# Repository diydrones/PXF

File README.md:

PXF ( current boards are 1.4)
===

This is the new Repository for the PXF Linux AutoPilot. 

This Project will allow the porting of ArduPilot to Linux, allowing us to add a multitude of other features to the Autopilot.

The actual Autopilot code will still be in the ArduPilot repo.<a href="https://github.com/diydrones/ardupilot" title="https://github.com/diydrones/ardupilot" target="https://github.com/diydrones/ardupilot"> https://github.com/diydrones/ardupilot</a>

This Repo will house the Hardware Schematics, Datasheets, and software specific to the PXF project.

Version 1 of this project is a cape for the BBB.

This project is for developers, it will NOT be supported by the DIYDrones or Ardupilot support forums for general users. 

This means we do not expect that this board will be plug and play, nor do we intend it to be.

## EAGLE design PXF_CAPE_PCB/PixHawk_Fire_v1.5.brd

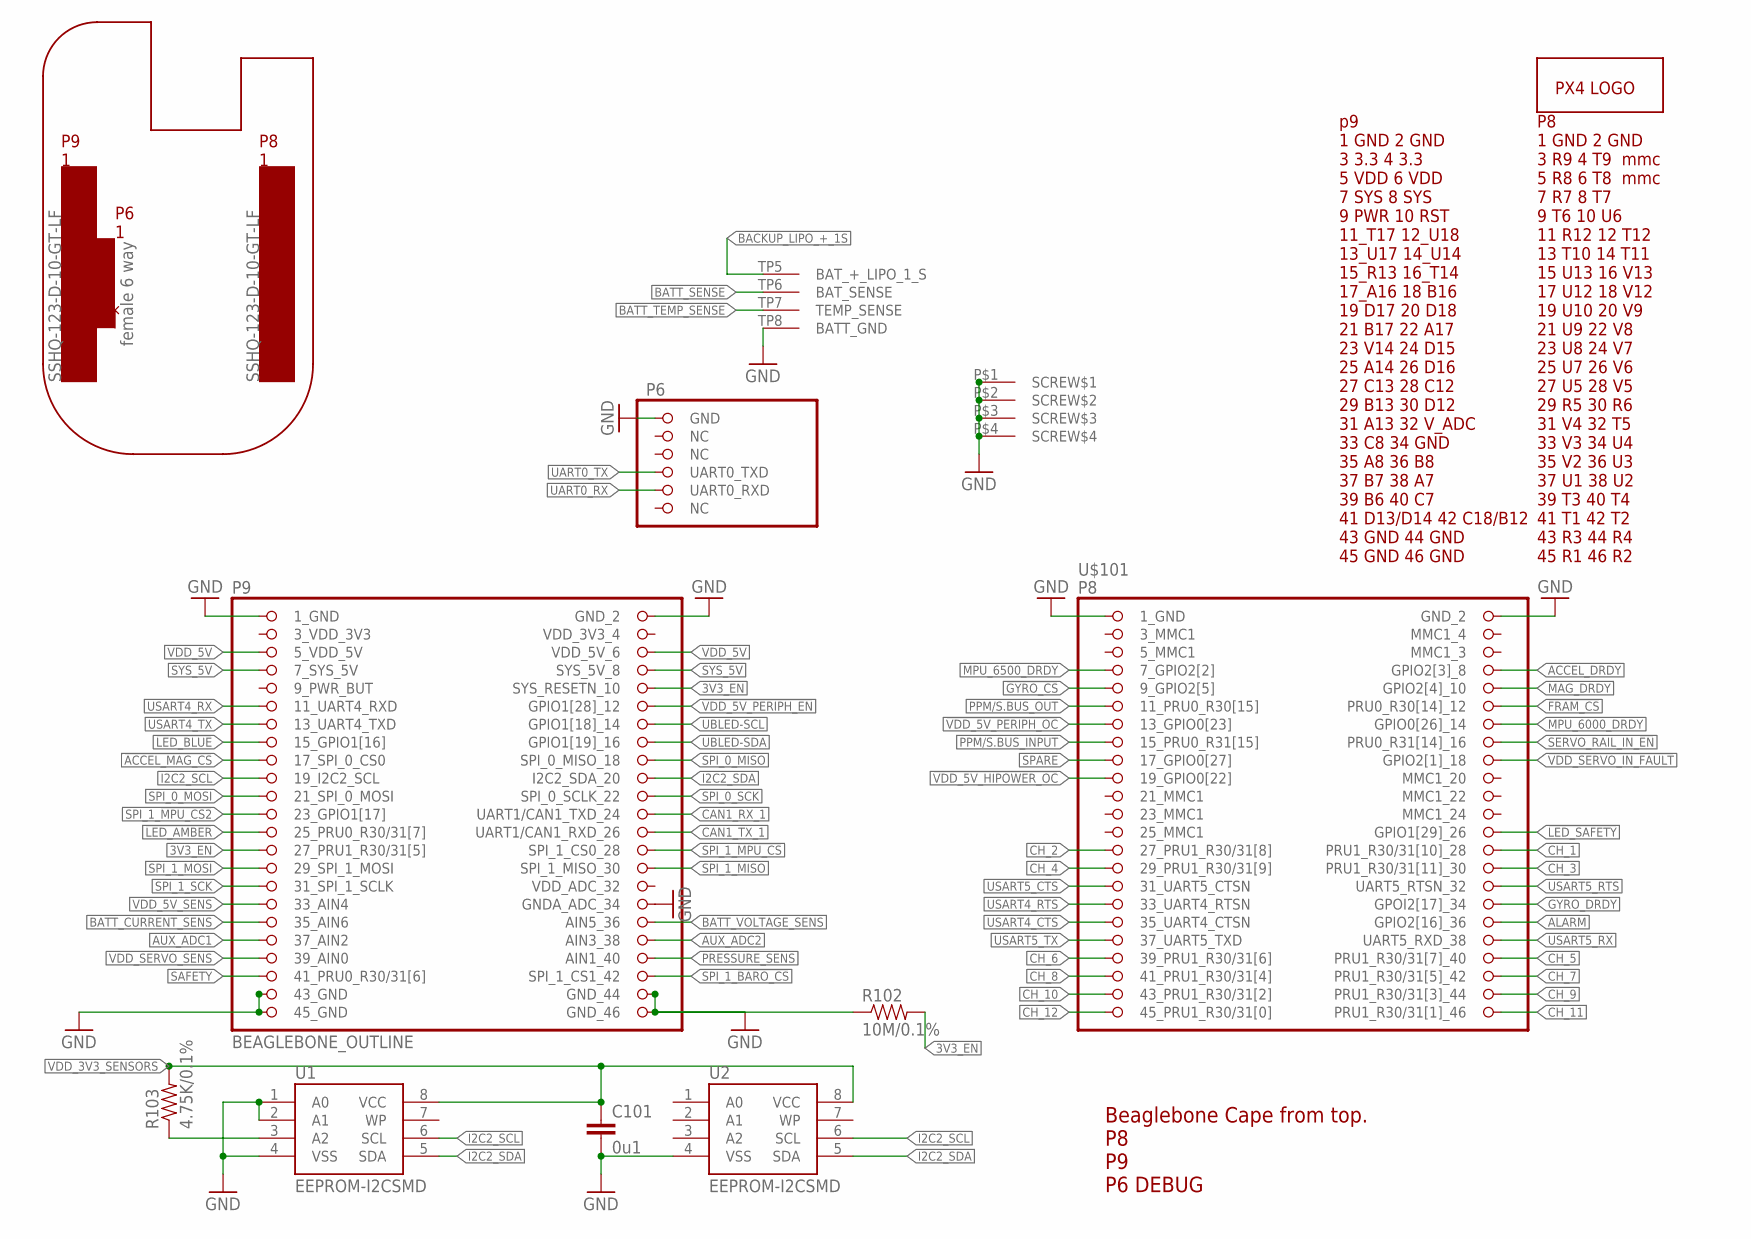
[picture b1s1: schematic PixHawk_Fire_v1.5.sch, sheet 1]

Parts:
C101: 0u1; 0402-CAP; PARTNO CC0402ZRY5V7BB104
R102: 10M/0.1%; 0402-RES; PARTNO RC0402FR-0710ML
R103: 4.75K/0.1%; 0402-RES; PARTNO RC0402FR-074K75L
U1: EEPROM-I2CSMD; SO08; PARTNO AT24CS32-SSHM
U2: EEPROM-I2CSMD; SO08; PARTNO ATSHA204-SH-DA-TTR-ND
U$1: PX4-LOGO; PIXHAWK-FIRE-LOGO-30
U$101: BEAGLEBONE_OUTLINE; BEAGLEBONE_SHIELD

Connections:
3V3_EN: R102.P$2 (2), U$101.56 (SYS_RESETN_10), U$101.73 (27_PRU1_R30/31[5]); also elsewhere on the board
3_VDD_3V3: U$101.49 (3_VDD_3V3)
!ACCEL_MAG_CS: U$101.63 (17_SPI_0_CS0); also elsewhere on the board
!FRAM_CS: U$101.12 (PRU0_R30[14]_12); also elsewhere on the board
!GYRO_CS: U$101.9 (9_GPIO2[5]); also elsewhere on the board
!LED_AMBER: U$101.71 (25_PRU0_R30/31[7]); also elsewhere on the board
!LED_BLUE: U$101.61 (15_GPIO1[16]); also elsewhere on the board
!LED_SAFETY: U$101.26 (GPIO1[29]_26); also elsewhere on the board
!VDD_5V_HIPOWER_OC: U$101.19 (19_GPIO0[22]); also elsewhere on the board
!VDD_5V_PERIPH_EN: U$101.58 (GPIO1[28]_12); also elsewhere on the board
!VDD_5V_PERIPH_OC: U$101.13 (13_GPIO0[23]); also elsewhere on the board
!VDD_SERVO_IN_FAULT: U$101.18 (GPIO2[1]_18)
ACCEL_DRDY: U$101.8 (GPIO2[3]_8); also elsewhere on the board
ALARM: U$101.36 (GPIO2[16]_36); also elsewhere on the board
AUX_ADC1: U$101.83 (37_AIN2); also elsewhere on the board
AUX_ADC2: U$101.84 (AIN3_38); also elsewhere on the board
BACKUP_LIPO_+_1S: U$101.TP5 (BAT_+_LIPO_1_S); also elsewhere on the board
BATT_CURRENT_SENS: U$101.81 (35_AIN6); also elsewhere on the board
BATT_SENSE: U$101.TP6 (BAT_SENSE); also elsewhere on the board
BATT_TEMP_SENSE: U$101.TP7 (TEMP_SENSE); also elsewhere on the board
BATT_VOLTAGE_SENS: U$101.82 (AIN5_36); also elsewhere on the board
CAN1_RX_1: U$101.70 (UART1/CAN1_TXD_24); also elsewhere on the board
CAN1_TX_1: U$101.72 (UART1/CAN1_RXD_26); also elsewhere on the board
CH_1: U$101.28 (PRU1_R30/31[10]_28); also elsewhere on the board
CH_2: U$101.27 (27_PRU1_R30/31[8]); also elsewhere on the board
CH_3: U$101.30 (PRU1_R30/31[11]_30); also elsewhere on the board
CH_4: U$101.29 (29_PRU1_R30/31[9]); also elsewhere on the board
CH_5: U$101.40 (PRU1_R30/31[7]_40); also elsewhere on the board
CH_6: U$101.39 (39_PRU1_R30/31[6]); also elsewhere on the board
CH_7: U$101.42 (PRU1_R30/31[5]_42); also elsewhere on the board
CH_8: U$101.41 (41_PRU1_R30/31[4]); also elsewhere on the board
CH_9: U$101.44 (PRU1_R30/31[3]_44); also elsewhere on the board
CH_10: U$101.43 (43_PRU1_R30/31[2]); also elsewhere on the board
CH_11: U$101.46 (PRU1_R30/31[1]_46); also elsewhere on the board
CH_12: U$101.45 (45_PRU1_R30/31[0]); also elsewhere on the board
GND: C101.P$2 (2), R102.P$1 (1), U1.1 (A0), U1.2 (A1), U1.4 (VSS), U2.4 (VSS), U$101.1 (1_GND), U$101.2 (GND_2), U$101.47 (1_GND), U$101.48 (GND_2), U$101.80 (GNDA_ADC_34), U$101.89 (43_GND), U$101.90 (GND_44), U$101.91 (45_GND), U$101.92 (GND_46), U$101.93 (GND), U$101.P$1 (SCREW$1), U$101.P$2 (SCREW$2), U$101.P$3 (SCREW$3), U$101.P$4 (SCREW$4), U$101.TP8 (BATT_GND); also elsewhere on the board
GYRO_DRDY: U$101.34 (GPOI2[17]_34); also elsewhere on the board
I2C2_SCL: U1.6 (SCL), U2.6 (SCL), U$101.65 (19_I2C2_SCL); also elsewhere on the board
I2C2_SDA: U1.5 (SDA), U2.5 (SDA), U$101.66 (I2C2_SDA_20); also elsewhere on the board
MAG_DRDY: U$101.10 (GPIO2[4]_10); also elsewhere on the board
MPU_6000_DRDY: U$101.14 (GPIO0[26]_14); also elsewhere on the board
MPU_6500_DRDY: U$101.7 (7_GPIO2[2]); also elsewhere on the board
unnamed: R103.P$1 (1), U1.3 (A2)
PPM/S.BUS_INPUT: U$101.15 (15_PRU0_R31[15]); also elsewhere on the board
PPM/S.BUS_OUT: U$101.11 (11_PRU0_R30[15]); also elsewhere on the board
PRESSURE_SENS: U$101.86 (AIN1_40); also elsewhere on the board
SAFETY: U$101.87 (41_PRU0_R30/31[6]); also elsewhere on the board
SERVO_RAIL_IN_!EN: U$101.16 (PRU0_R31[14]_16)
SPARE: U$101.17 (17_GPIO0[27])
SPI_0_MISO: U$101.64 (SPI_0_MISO_18); also elsewhere on the board
SPI_0_MOSI: U$101.67 (21_SPI_0_MOSI); also elsewhere on the board
SPI_0_SCK: U$101.68 (SPI_0_SCLK_22); also elsewhere on the board
SPI_1_!BARO_CS: U$101.88 (SPI_1_CS1_42); also elsewhere on the board
SPI_1_!MPU_CS: U$101.74 (SPI_1_CS0_28); also elsewhere on the board
SPI_1_!MPU_CS2: U$101.69 (23_GPIO1[17]); also elsewhere on the board
SPI_1_MISO: U$101.76 (SPI_1_MISO_30); also elsewhere on the board
SPI_1_MOSI: U$101.75 (29_SPI_1_MOSI); also elsewhere on the board
SPI_1_SCK: U$101.77 (31_SPI_1_SCLK); also elsewhere on the board
SYS_5V: U$101.53 (7_SYS_5V), U$101.54 (SYS_5V_8); also elsewhere on the board
UART0_RX: U$101.97 (UART0_RXD); also elsewhere on the board
UART0_TX: U$101.96 (UART0_TXD); also elsewhere on the board
UBLED-SCL: U$101.60 (GPIO1[18]_14); also elsewhere on the board
UBLED-SDA: U$101.62 (GPIO1[19]_16); also elsewhere on the board
USART4_CTS: U$101.35 (35_UART4_CTSN); also elsewhere on the board
USART4_RTS: U$101.33 (33_UART4_RTSN); also elsewhere on the board
USART4_RX: U$101.57 (11_UART4_RXD); also elsewhere on the board
USART4_TX: U$101.59 (13_UART4_TXD); also elsewhere on the board
USART5_CTS: U$101.31 (31_UART5_CTSN); also elsewhere on the board
USART5_RTS: U$101.32 (UART5_RTSN_32); also elsewhere on the board
USART5_RX: U$101.38 (UART5_RXD_38); also elsewhere on the board
USART5_TX: U$101.37 (37_UART5_TXD); also elsewhere on the board
VDD_3V3_4: U$101.50 (VDD_3V3_4)
VDD_3V3_SENSORS: C101.P$1 (1), R103.P$2 (2), U1.8 (VCC), U2.8 (VCC); also elsewhere on the board
VDD_5V: U$101.51 (5_VDD_5V), U$101.52 (VDD_5V_6); also elsewhere on the board
VDD_5V_SENS: U$101.79 (33_AIN4); also elsewhere on the board
VDD_SERVO_SENS: U$101.85 (39_AIN0); also elsewhere on the board

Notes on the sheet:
Beaglebone Cape from top. P8 P9 P6 DEBUG

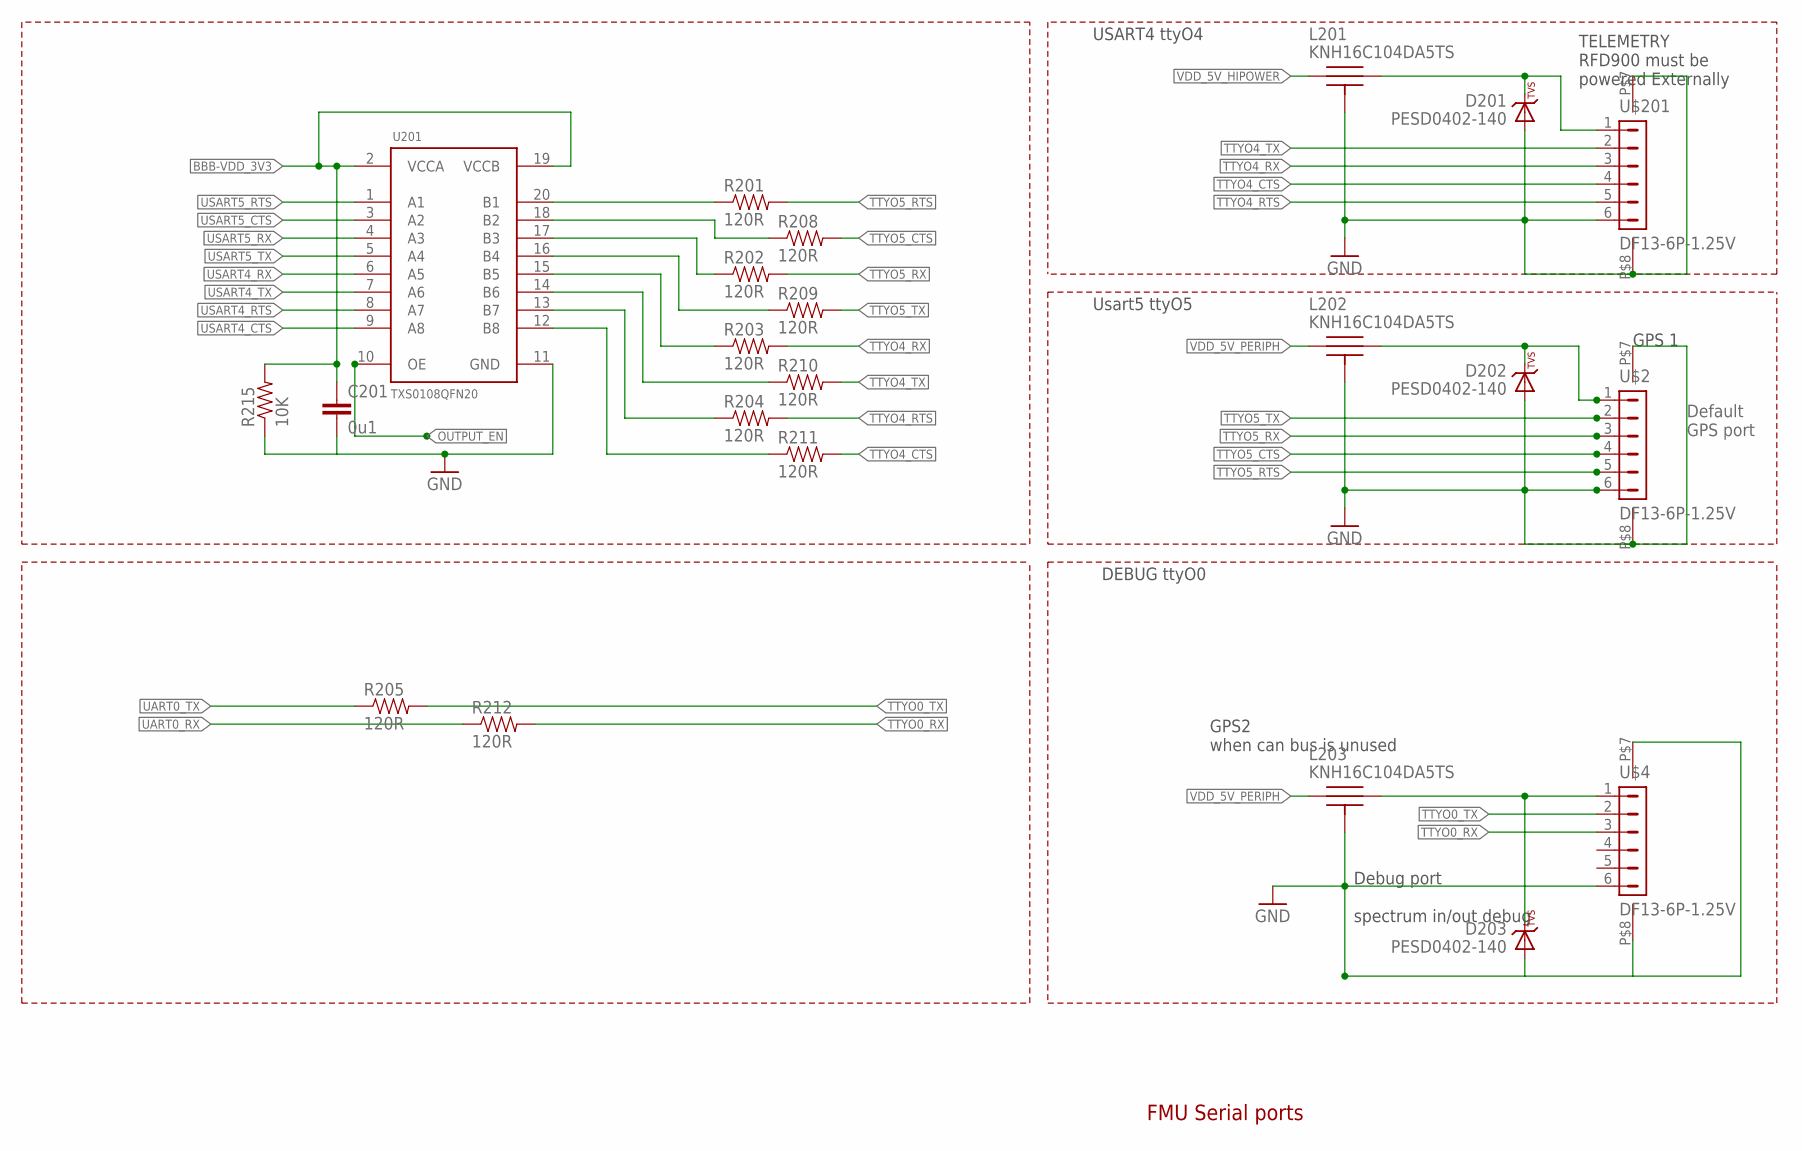
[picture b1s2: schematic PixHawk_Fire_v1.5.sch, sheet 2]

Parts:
C201: 0u1; 0402-CAP; PARTNO CC0402ZRY5V7BB104
D201, D202, D203: PESD0402-140; 0402-TVS; PARTNO PESD0402-140
L201, L202, L203: KNH16C104DA5TS; KYOCERA-KNH16-DA; PARTNO KNH16C104DA5TS
R201, R202, R203, R204, R205, R208, R209, R210, R211, R212: 120R; 0402-RES; PARTNO RC0402FR-07120RL
R215: 10K; 0402-RES; PARTNO ERA-2AEB103X
U201: TXS0108QFN20; QFN20-RGY; PARTNO TXS0108ERGYR
U$2, U$4, U$201: DF13-6P-1.25V; DF13C-6P-1.25V; PARTNO DF13C-6P-1.25V(20)

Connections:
BBB-VDD_3V3: C201.P$1 (1), R215.P$2 (2), U201.2 (VCCA), U201.19 (VCCB); also elsewhere on the board
GND: C201.P$2 (2), D201.A, D202.A, D203.A, L201.P$3, L201.P$4, L201.P$5, L202.P$3, L202.P$4, L202.P$5, L203.P$3, L203.P$4, L203.P$5, R215.P$1 (1), U201.11 (GND), U$2.6, U$2.P$7, U$2.P$8, U$4.6, U$4.P$7, U$4.P$8, U$201.6, U$201.P$7, U$201.P$8; also elsewhere on the board
unnamed: D201.C, L201.P$2, U$201.1
unnamed: R208.P$1 (1), U201.18 (B2)
unnamed: R201.P$1 (1), U201.20 (B1)
unnamed: R202.P$1 (1), U201.17 (B3)
unnamed: R209.P$1 (1), U201.16 (B4)
unnamed: R203.P$1 (1), U201.15 (B5)
unnamed: R210.P$1 (1), U201.14 (B6)
unnamed: R204.P$1 (1), U201.13 (B7)
unnamed: R211.P$1 (1), U201.12 (B8)
unnamed: D203.C, L203.P$2, U$4.1
unnamed: D202.C, L202.P$2, U$2.1
OUTPUT_EN: U201.10 (OE); also elsewhere on the board
TTYO0_RX: R212.P$2 (2), U$4.3
TTYO0_TX: R205.P$2 (2), U$4.2
TTYO4_CTS: R211.P$2 (2), U$201.4
TTYO4_RTS: R204.P$2 (2), U$201.5
TTYO4_RX: R203.P$2 (2), U$201.3; also elsewhere on the board
TTYO4_TX: R210.P$2 (2), U$201.2; also elsewhere on the board
TTYO5_CTS: R208.P$2 (2), U$2.4
TTYO5_RTS: R201.P$2 (2), U$2.5
TTYO5_RX: R202.P$2 (2), U$2.3; also elsewhere on the board
TTYO5_TX: R209.P$2 (2), U$2.2; also elsewhere on the board
UART0_RX: R212.P$1 (1); also elsewhere on the board
UART0_TX: R205.P$1 (1); also elsewhere on the board
USART4_CTS: U201.9 (A8); also elsewhere on the board
USART4_RTS: U201.8 (A7); also elsewhere on the board
USART4_RX: U201.6 (A5); also elsewhere on the board
USART4_TX: U201.7 (A6); also elsewhere on the board
USART5_CTS: U201.3 (A2); also elsewhere on the board
USART5_RTS: U201.1 (A1); also elsewhere on the board
USART5_RX: U201.4 (A3); also elsewhere on the board
USART5_TX: U201.5 (A4); also elsewhere on the board
VDD_5V_HIPOWER: L201.P$1; also elsewhere on the board
VDD_5V_PERIPH: L202.P$1, L203.P$1; also elsewhere on the board

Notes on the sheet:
FMU Serial ports
Usart5 ttyO5
USART4 ttyO4
DEBUG ttyO0
Default GPS port
TELEMETRY RFD900 must be powered Externally
GPS 1
Debug port spectrum in/out debug
GPS2 when can bus is unused

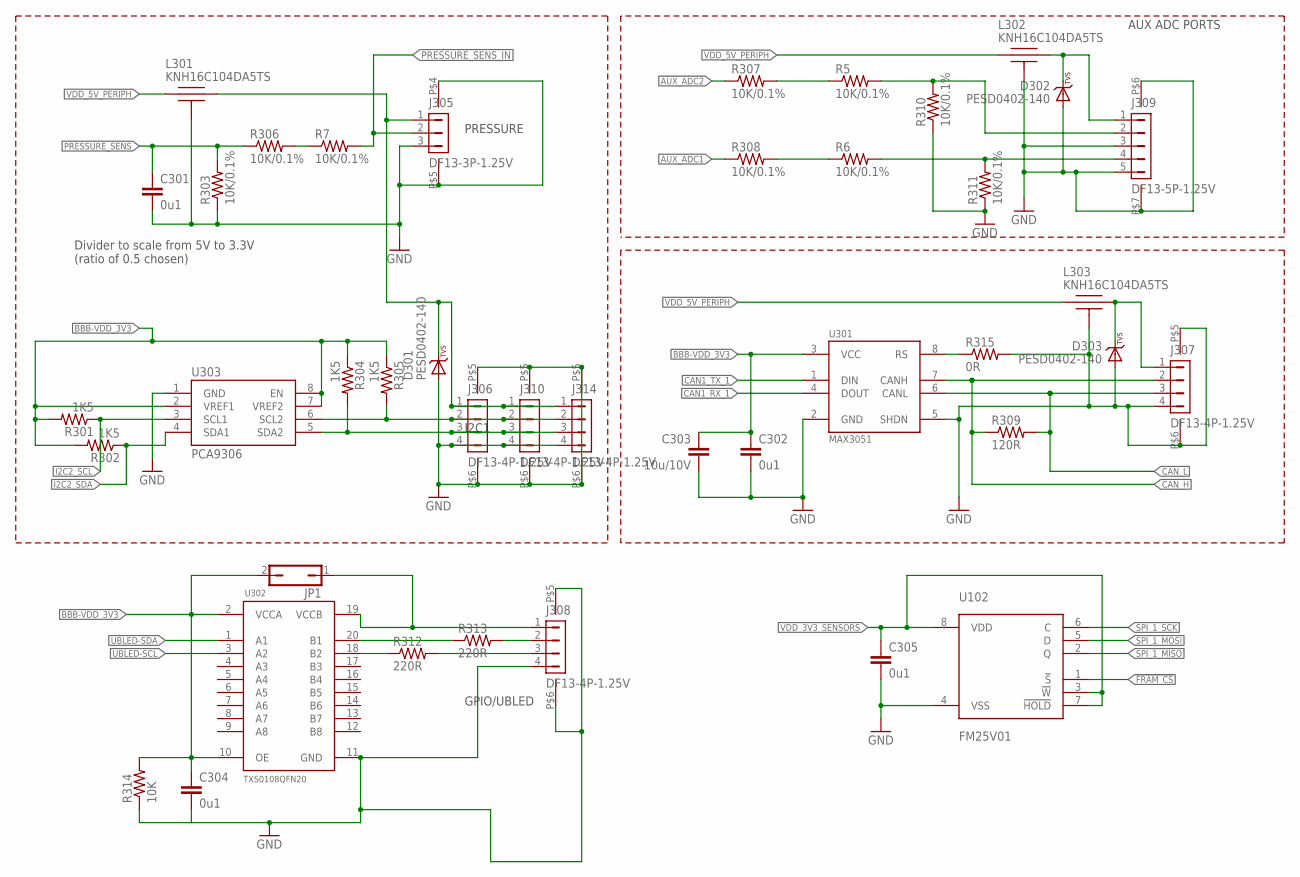
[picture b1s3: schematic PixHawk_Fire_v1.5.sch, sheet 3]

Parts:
C301, C302, C304, C305: 0u1; 0402-CAP; PARTNO CC0402ZRY5V7BB104
C303: 10u/10V; 0805-CAP; PARTNO CC0805ZKY5V6BB106
D301, D302, D303: PESD0402-140; 0402-TVS; PARTNO PESD0402-140
J305: DF13-3P-1.25V; DF13C-3P-1.25V; PARTNO DF13C-3P-1.25V(20)
J306, J307, J308, J310, J314: DF13-4P-1.25V; DF13C-4P-1.25V; PARTNO DF13C-4P-1.25V(20)
J309: DF13-5P-1.25V; DF13C-5P-1.25V; PARTNO DF13C-5P-1.25V(20)
JP1: JP1Q; JP1; PARTNO 1-87215-0
L301, L302, L303: KNH16C104DA5TS; KYOCERA-KNH16-DA; PARTNO KNH16C104DA5TS
R5, R6, R7, R303, R306, R307, R308, R310, R311: 10K/0.1%; 0402-RES; PARTNO ERA-2AEB103X
R301, R302, R304, R305: 1K5; 0402-RES; PARTNO RC0402FR-071K5L
R309: 120R; 0402-RES; PARTNO RC0402FR-07120RL
R312, R313: 220R; 0402-RES; PARTNO RC0402FR-07220RL
R314: 10K; 0402-RES; PARTNO ERA-2AEB103X
R315: 0R; 0402-RES; PARTNO RC0402FR-070RL
U102: FM25V01; SO08; PARTNO FM25V01-G
U301: MAX3051; SOT23-8; PARTNO MAX3051EKA
U302: TXS0108QFN20; QFN20-RGY; PARTNO TXS0108ERGYR
U303: PCA9306; PARTNO PCA9306DQER

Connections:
!FRAM_CS: U102.1 (!S); also elsewhere on the board
AUX_ADC1: R308.P$1 (1); also elsewhere on the board
AUX_ADC2: R307.P$1 (1); also elsewhere on the board
BBB-VDD_3V3: C302.P$1 (1), C303.P$1 (1), C304.P$1 (1), JP1.2, R301.P$2 (2), R302.P$2 (2), R304.P$1 (1), R305.P$1 (1), R314.P$2 (2), U301.3 (VCC), U302.2 (VCCA), U302.10 (OE), U303.2 (VREF1), U303.7 (VREF2), U303.8 (EN); also elsewhere on the board
CAN1_RX_1: U301.4 (DOUT); also elsewhere on the board
CAN1_TX_1: U301.1 (DIN); also elsewhere on the board
CAN_H: J307.2, R309.P$1 (1), U301.7 (CANH); also elsewhere on the board
CAN_L: J307.3, R309.P$2 (2), U301.6 (CANL); also elsewhere on the board
FMU_AUX_ADC1_PROT: J309.4, R6.P$2 (2), R311.P$2 (2)
FMU_AUX_ADC2_PROT: J309.2, R5.P$2 (2), R310.P$2 (2)
GND: C301.P$2 (2), C302.P$2 (2), C303.P$2 (2), C304.P$2 (2), C305.P$2 (2), D301.A, D302.A, D303.A, J305.3, J305.P$4, J305.P$5, J306.4, J306.P$5, J306.P$6, J307.4, J307.P$5, J307.P$6, J308.4, J308.P$5, J308.P$6, J309.3, J309.5, J309.P$6, J309.P$7, J310.4, J310.P$5, J310.P$6, J314.4, J314.P$5, J314.P$6, L301.P$3, L301.P$4, L301.P$5, L302.P$3, L302.P$4, L302.P$5, L303.P$3, L303.P$4, L303.P$5, R303.P$1 (1), R310.P$1 (1), R311.P$1 (1), R314.P$1 (1), R315.P$2 (2), U102.4 (VSS), U301.2 (GND), U301.5 (SHDN), U302.11 (GND), U303.1 (GND); also elsewhere on the board
I2C2_SCL: R301.P$1 (1), U303.3 (SCL1); also elsewhere on the board
I2C2_SDA: R302.P$1 (1), U303.4 (SDA1); also elsewhere on the board
unnamed: R313.P$1 (1), U302.20 (B1)
unnamed: J306.2, J310.2, J314.2, R305.P$2 (2), U303.6 (SCL2)
unnamed: J306.3, J310.3, J314.3, R304.P$2 (2), U303.5 (SDA2)
unnamed: R312.P$1 (1), U302.18 (B2)
unnamed: D301.C, J305.1, J306.1, J310.1, J314.1, L301.P$2
unnamed: J308.3, R312.P$2 (2)
unnamed: J308.2, R313.P$2 (2)
unnamed: J308.1, JP1.1, U302.19 (VCCB)
unnamed: D303.C, J307.1, L303.P$2
unnamed: R315.P$1 (1), U301.8 (RS)
unnamed: R5.P$1 (1), R307.P$2 (2)
unnamed: R6.P$1 (1), R308.P$2 (2)
unnamed: R7.P$1 (1), R306.P$2 (2)
unnamed: D302.C, J309.1, L302.P$2
PRESSURE_SENS: C301.P$1 (1), R303.P$2 (2), R306.P$1 (1); also elsewhere on the board
PRESSURE_SENS_IN: J305.2, R7.P$2 (2); also elsewhere on the board
SPI_1_MISO: U102.2 (Q); also elsewhere on the board
SPI_1_MOSI: U102.5 (D); also elsewhere on the board
SPI_1_SCK: U102.6 (C); also elsewhere on the board
UBLED-SCL: U302.3 (A2); also elsewhere on the board
UBLED-SDA: U302.1 (A1); also elsewhere on the board
VDD_3V3_SENSORS: C305.P$1 (1), U102.3 (!W), U102.7 (!HOLD), U102.8 (VDD); also elsewhere on the board
VDD_5V_PERIPH: L301.P$1, L302.P$1, L303.P$1; also elsewhere on the board

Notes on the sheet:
PRESSURE
I2C1
AUX ADC PORTS
Divider to scale from 5V to 3.3V (ratio of 0.5 chosen)
GPIO/UBLED

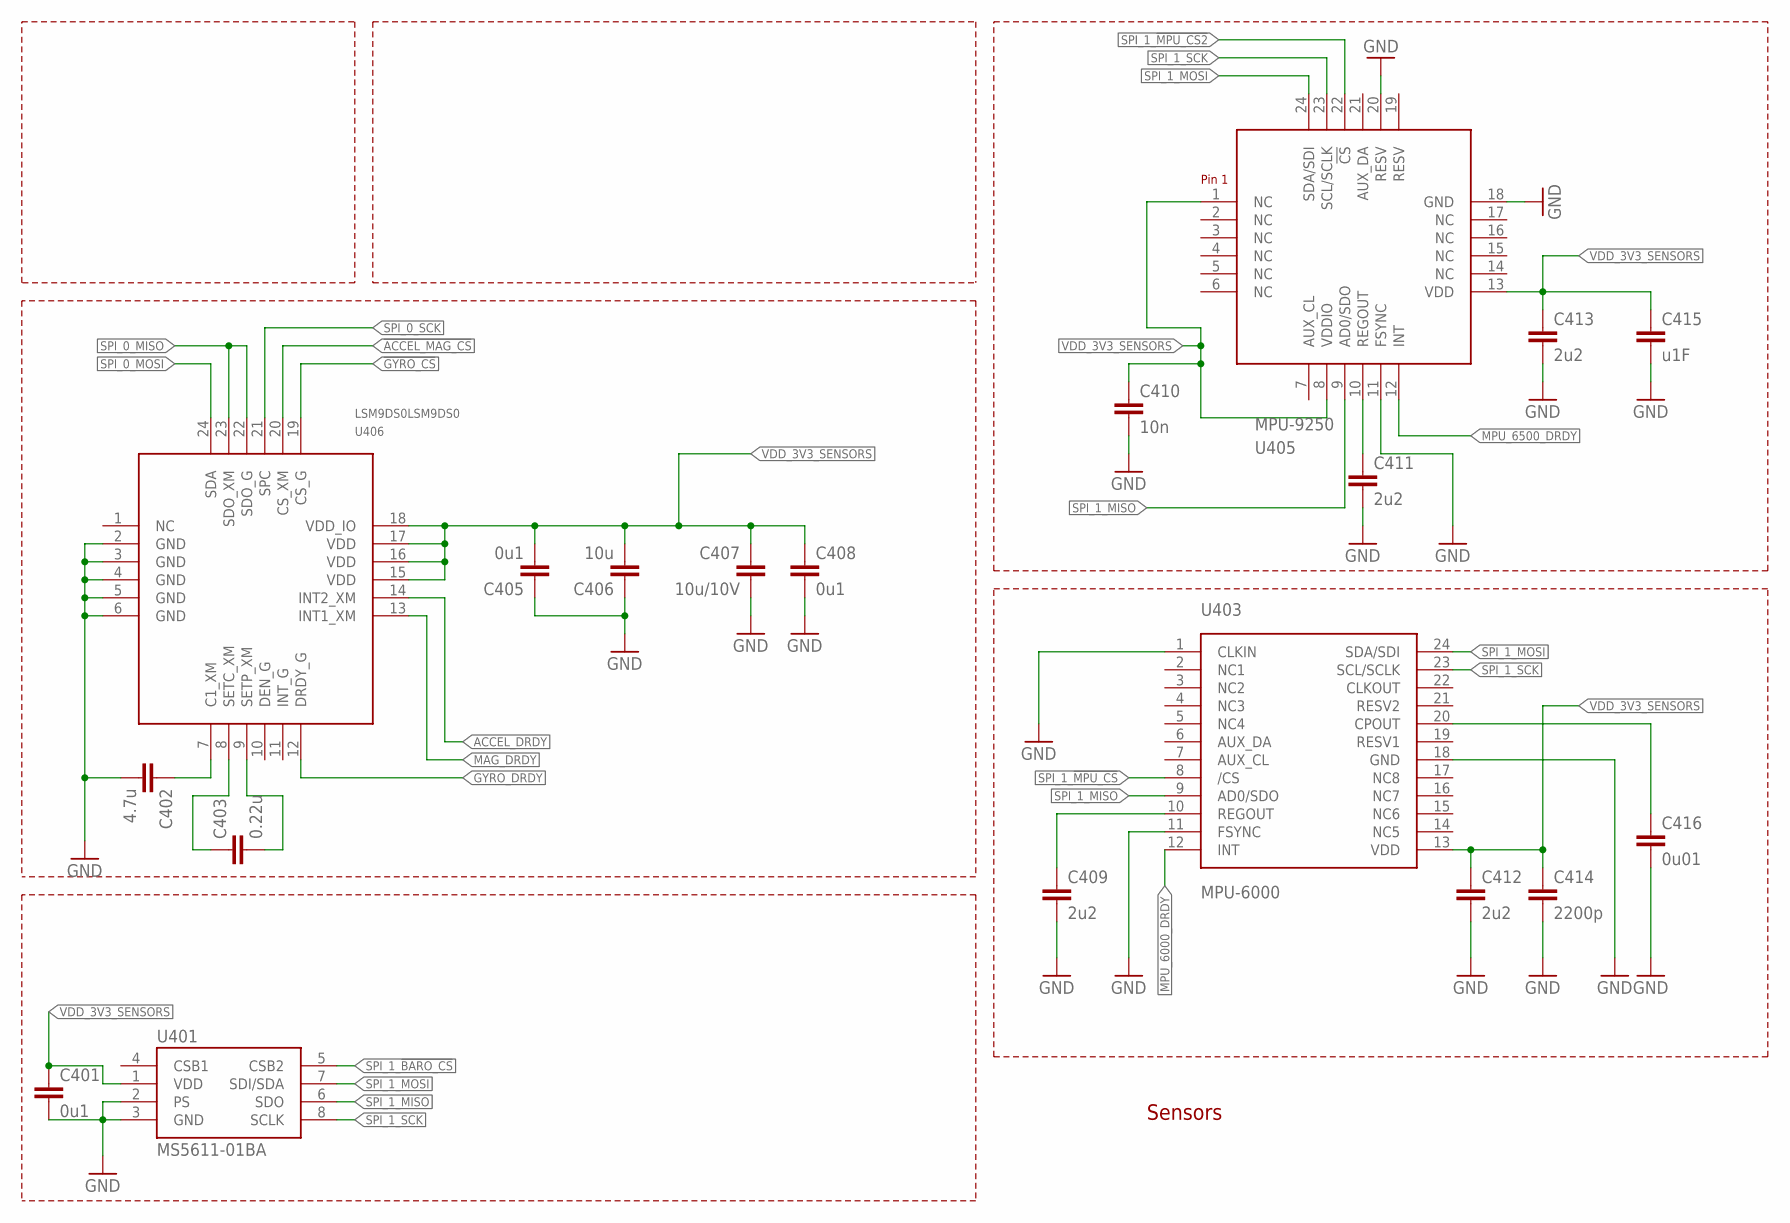
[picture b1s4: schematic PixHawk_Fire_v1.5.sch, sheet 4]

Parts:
C401, C408: 0u1; 0402-CAP; PARTNO CC0402ZRY5V7BB104
C402: 4.7u; 0603-CAP; PARTNO C1608X7S1A475K080AC
C403: 0.22u; 0603-CAP; PARTNO CL10B224JP8NNNC
C405: 0u1; 0603-CAP; PARTNO CL10B104JO8NNNC
C406: 10u; 0603-CAP; PARTNO C1608X7S0J106M080AC
C407: 10u/10V; 0805-CAP; PARTNO CC0805ZKY5V6BB106
C409, C411: 2u2; 0603-CAP; PARTNO C1608X6S1C225K080AC
C410: 10n; 0603-CAP; PARTNO C0603C103J5RAC7411
C412: 2u2; 0603-CAP; PARTNO CGA3E1X7R0J225K080AC
C413: 2u2; 0603-CAP
C414: 2200p; 0402-CAP; PARTNO C0603C222J5RACTU
C415: u1F; 0402-CAP; PARTNO CC0402ZRY5V7BB104
C416: 0u01; 0603-CAP; PARTNO 06033C103JAT2A
U401: MS5611-01BA; PARTNO MS5611-01BA
U403: MPU-6000; QFN-24; PARTNO MPU-6000
U405: MPU-9250; MPU-6500; PARTNO MPU-9250
U406: LSM9DS0LSM9DS0; LSM9DS0; PARTNO LSM9DS0TR

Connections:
!ACCEL_MAG_CS: U406.20 (CS_XM); also elsewhere on the board
!GYRO_CS: U406.19 (CS_G); also elsewhere on the board
ACCEL_DRDY: U406.14 (INT2_XM); also elsewhere on the board
GND: C401.P$2 (2), C402.P$2 (2), C405.P$1 (1), C406.P$1 (1), C407.P$2 (2), C408.P$2 (2), C409.P$2 (2), C410.P$2 (2), C411.P$2 (2), C412.P$2 (2), C413.P$2 (2), C414.P$2 (2), C415.P$2 (2), C416.P$2 (2), U401.2 (PS), U401.3 (GND), U403.1 (CLKIN), U403.11 (FSYNC), U403.18 (GND), U405.11 (FSYNC), U405.18 (GND), U405.20 (RESV), U406.2 (GND), U406.3 (GND), U406.4 (GND), U406.5 (GND), U406.6 (GND); also elsewhere on the board
GYRO_DRDY: U406.12 (DRDY_G); also elsewhere on the board
MAG_DRDY: U406.13 (INT1_XM); also elsewhere on the board
MPU_6000_DRDY: U403.12 (INT); also elsewhere on the board
MPU_6500_DRDY: U405.12 (INT); also elsewhere on the board
unnamed: C402.P$1 (1), U406.7 (C1_XM)
unnamed: C403.P$2 (2), U406.9 (SETP_XM)
unnamed: C411.P$1 (1), U405.10 (REGOUT)
unnamed: C403.P$1 (1), U406.8 (SETC_XM)
unnamed: C409.P$1 (1), U403.10 (REGOUT)
unnamed: C416.P$1 (1), U403.20 (CPOUT)
SPI_0_MISO: U406.22 (SDO_G), U406.23 (SDO_XM); also elsewhere on the board
SPI_0_MOSI: U406.24 (SDA); also elsewhere on the board
SPI_0_SCK: U406.21 (SPC); also elsewhere on the board
SPI_1_!BARO_CS: U401.5 (CSB2); also elsewhere on the board
SPI_1_!MPU_CS: U403.8 (/CS); also elsewhere on the board
SPI_1_!MPU_CS2: U405.22 (!CS); also elsewhere on the board
SPI_1_MISO: U401.6 (SDO), U403.9 (AD0/SDO), U405.9 (AD0/SDO); also elsewhere on the board
SPI_1_MOSI: U401.7 (SDI/SDA), U403.24 (SDA/SDI), U405.24 (SDA/SDI); also elsewhere on the board
SPI_1_SCK: U401.8 (SCLK), U403.23 (SCL/SCLK), U405.23 (SCL/SCLK); also elsewhere on the board
VDD_3V3_SENSORS: C401.P$1 (1), C405.P$2 (2), C406.P$2 (2), C407.P$1 (1), C408.P$1 (1), C410.P$1 (1), C412.P$1 (1), C413.P$1 (1), C414.P$1 (1), C415.P$1 (1), U401.1 (VDD), U403.13 (VDD), U405.1 (NC), U405.8 (VDDIO), U405.13 (VDD), U406.15 (VDD), U406.16 (VDD), U406.17 (VDD), U406.18 (VDD_IO); also elsewhere on the board

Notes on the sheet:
Sensors

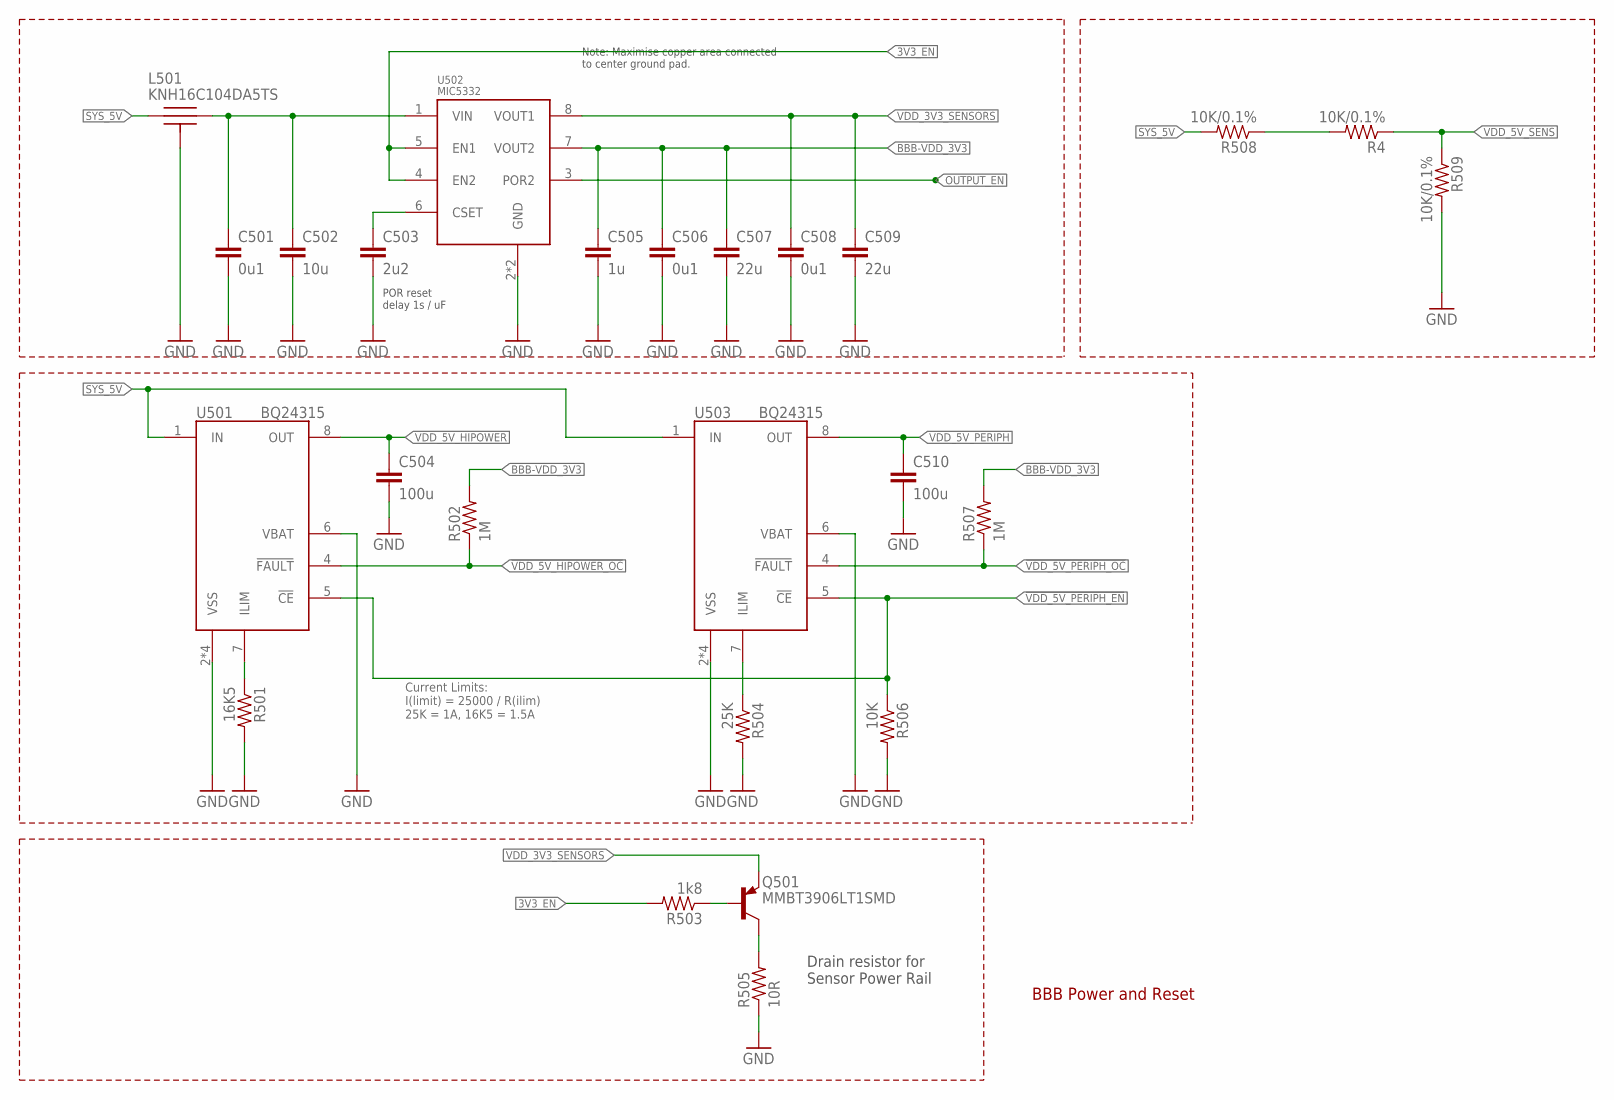
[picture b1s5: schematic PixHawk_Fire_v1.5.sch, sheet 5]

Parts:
C501, C506, C508: 0u1; 0402-CAP; PARTNO CC0402ZRY5V7BB104
C502: 10u; 0805-CAP; PARTNO C1608X7S0J106M080AC
C503: 2u2; 0603-CAP; PARTNO C1608X6S1C225K080AC
C504, C510: 100u; 1206-CAP; PARTNO C3216X5R1A107M160AC
C505: 1u; 0603-CAP; PARTNO CC0603ZRY5V7BB105
C507, C509: 22u; 0805-CAP; PARTNO CC0805MKX5R5BB226
L501: KNH16C104DA5TS; KYOCERA-KNH16-DA; PARTNO KNH16C104DA5TS
Q501: MMBT3906LT1SMD; SOT23-BEC; PARTNO MMBT3906LT1G
R4, R508, R509: 10K/0.1%; 0402-RES; PARTNO ERA-2AEB103X
R501: 16K5; 0402-RES; PARTNO RMCF0402FT16K5
R502, R507: 1M; 0402-RES; PARTNO MCR01MRTF1004
R503: 1k8; 0402-RES; PARTNO RC0402FR-071K8L
R504: 25K; 0402-RES; PARTNO RMCF0402FT25K5
R505: 10R; 0603-RES; PARTNO RC0402FR-0710RL
R506: 10K; 0402-RES; PARTNO ERA-2AEB103X
U501, U503: BQ24315; QFN8-DSG; PARTNO BQ24315DSGR
U502: MIC5332; MLF-8-EPAD; PARTNO MIC5332-SSYMT

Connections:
3V3_EN: R503.P$2 (2), U502.4 (EN2), U502.5 (EN1); also elsewhere on the board
!VDD_5V_HIPOWER_OC: R502.P$1 (1), U501.4 (!FAULT); also elsewhere on the board
!VDD_5V_PERIPH_EN: R506.P$1 (1), U501.5 (!CE), U503.5 (!CE); also elsewhere on the board
!VDD_5V_PERIPH_OC: R507.P$1 (1), U503.4 (!FAULT); also elsewhere on the board
BBB-VDD_3V3: C505.P$1 (1), C506.P$1 (1), C507.P$1 (1), R502.P$2 (2), R507.P$2 (2), U502.7 (VOUT2); also elsewhere on the board
FMU-VDD_5V5: C501.P$1 (1), C502.P$1 (1), L501.P$2, U502.1 (VIN)
GND: C501.P$2 (2), C502.P$2 (2), C503.P$2 (2), C504.P$2 (2), C505.P$2 (2), C506.P$2 (2), C507.P$2 (2), C508.P$2 (2), C509.P$2 (2), C510.P$2 (2), L501.P$3, L501.P$4, L501.P$5, R501.P$2 (2), R504.P$2 (2), R505.1, R506.P$2 (2), R509.P$2 (2), U501.2 (VSS), U501.6 (VBAT), U501.GND (VSS), U501.P$2 (VSS), U501.P$3 (VSS), U502.2 (GND), U502.GND, U503.2 (VSS), U503.6 (VBAT), U503.GND (VSS), U503.P$2 (VSS), U503.P$3 (VSS); also elsewhere on the board
unnamed: C503.P$1 (1), U502.6 (CSET)
unnamed: R504.P$1 (1), U503.7 (ILIM)
unnamed: R4.P$2 (2), R508.P$1 (1)
unnamed: Q501.C, R505.2
unnamed: Q501.B, R503.P$1 (1)
unnamed: R501.P$1 (1), U501.7 (ILIM)
OUTPUT_EN: U502.3 (POR2); also elsewhere on the board
SYS_5V: L501.P$1, R508.P$2 (2), U501.1 (IN), U503.1 (IN); also elsewhere on the board
VDD_3V3_SENSORS: C508.P$1 (1), C509.P$1 (1), Q501.E, U502.8 (VOUT1); also elsewhere on the board
VDD_5V_HIPOWER: C504.P$1 (1), U501.8 (OUT); also elsewhere on the board
VDD_5V_PERIPH: C510.P$1 (1), U503.8 (OUT); also elsewhere on the board
VDD_5V_SENS: R4.P$1 (1), R509.P$1 (1); also elsewhere on the board

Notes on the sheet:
BBB Power and Reset
Note: Maximise copper area connected to center ground pad.
POR reset delay 1s / uF
Current Limits: I(limit) = 25000 / R(ilim) 25K = 1A, 16K5 = 1.5A
Drain resistor for Sensor Power Rail

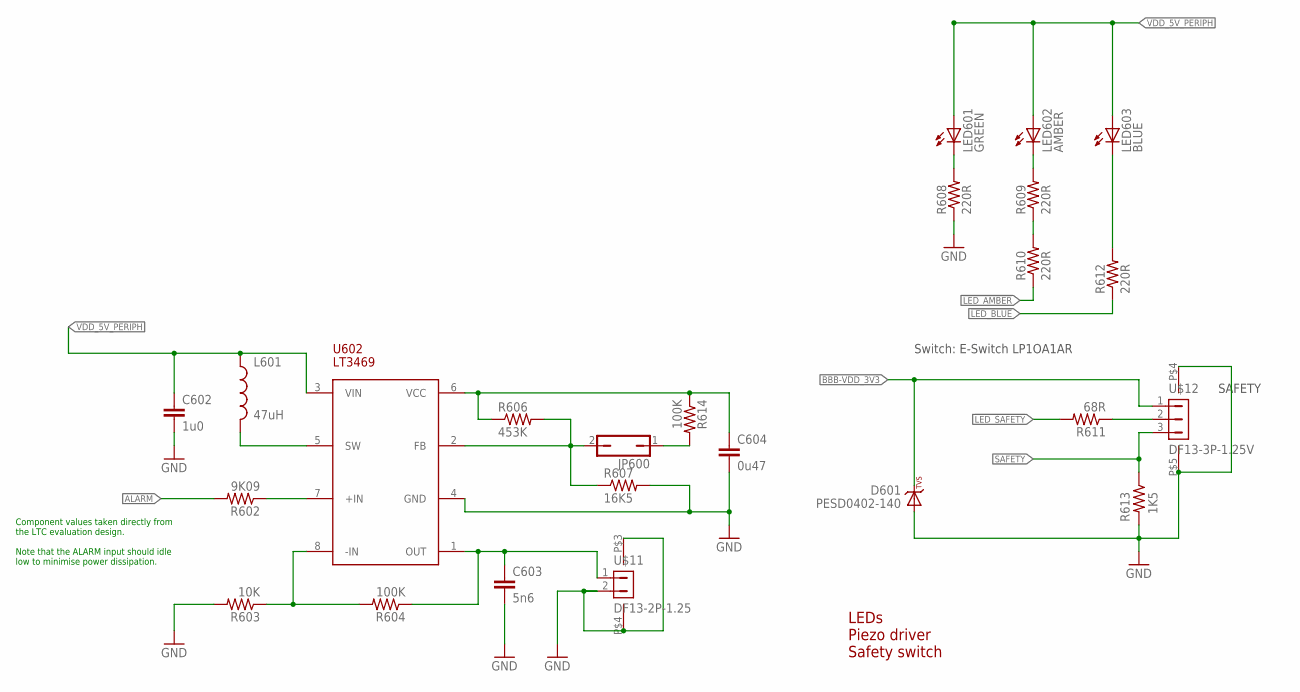
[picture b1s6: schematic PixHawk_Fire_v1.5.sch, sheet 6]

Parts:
C602: 1u0; 0603-CAP; PARTNO CC0603ZRY5V7BB105
C603: 5n6; 0402-CAP; PARTNO CC0402KRX7R7BB562
C604: 0u47; 0402-CAP; PARTNO C1005X5R1C474K050BC
D601: PESD0402-140; 0402-TVS; PARTNO PESD0402-140
JP600: JP1Q; JP1; PARTNO 1-87215-0
L601: 47uH; 0805-IND; PARTNO MLZ2012M470W
LED601: GREEN; 0603-LED; PARTNO APTD1608CGCK
LED602: AMBER; 0603-LED; PARTNO APTD1608SECK
LED603: BLUE; 0603-LED; PARTNO APTD1608QBC/D
R602: 9K09; 0402-RES; PARTNO RMCF0402FT9K09
R603: 10K; 0402-RES; PARTNO ERA-2AEB103X
R604, R614: 100K; 0402-RES; PARTNO RC0402FR-07100KL
R606: 453K; 0402-RES; PARTNO RMCF0402FT453K
R607: 16K5; 0402-RES; PARTNO RMCF0402FT16K5
R608, R609, R610, R612: 220R; 0402-RES; PARTNO RC0402FR-07220RL
R611: 68R; 0402-RES; PARTNO RC0402FR-0768RL
R613: 1K5; 0402-RES; PARTNO RC0402FR-071K5L
U602: LT3469; SOT23-8; PARTNO LT3469ETS8
U$11: DF13-2P-1.25; DF13C-2P-1.25V; PARTNO DF13C-2P-1.25V(20)
U$12: DF13-3P-1.25V; DF13C-3P-1.25V; PARTNO DF13C-3P-1.25V(20)

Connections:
!LED_AMBER: R610.P$1 (1); also elsewhere on the board
!LED_BLUE: R612.P$1 (1); also elsewhere on the board
!LED_SAFETY: R611.P$2 (2); also elsewhere on the board
ALARM: R602.P$2 (2); also elsewhere on the board
BBB-VDD_3V3: D601.C, U$12.1; also elsewhere on the board
GND: C602.P$2 (2), C603.P$2 (2), C604.P$2 (2), D601.A, R603.P$2 (2), R607.P$2 (2), R608.P$1 (1), R613.P$2 (2), U602.4 (GND), U$11.2, U$11.P$3, U$11.P$4, U$12.P$4, U$12.P$5; also elsewhere on the board
unnamed: LED603.C, R612.P$2 (2)
unnamed: JP600.2, R606.P$2 (2), R607.P$1 (1), U602.2 (FB)
unnamed: R603.P$1 (1), R604.P$2 (2), U602.8 (-IN)
unnamed: C603.P$1 (1), R604.P$1 (1), U602.1 (OUT), U$11.1
unnamed: R602.P$1 (1), U602.7 (+IN)
unnamed: LED601.C, R608.P$2 (2)
unnamed: L601.P$2 (2), U602.5 (SW)
unnamed: C604.P$1 (1), R606.P$1 (1), R614.P$1 (1), U602.6 (VCC)
unnamed: R609.P$1 (1), R610.P$2 (2)
unnamed: LED602.C, R609.P$2 (2)
unnamed: JP600.1, R614.P$2 (2)
unnamed: R611.P$1 (1), U$12.2
SAFETY: R613.P$1 (1), U$12.3; also elsewhere on the board
VDD_5V_PERIPH: C602.P$1 (1), L601.P$1 (1), LED601.A, LED602.A, LED603.A, U602.3 (VIN); also elsewhere on the board

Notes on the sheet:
LEDs Piezo driver Safety switch
Switch: E-Switch LP1OA1AR
SAFETY
Component values taken directly from the LTC evaluation design. Note that the ALARM input should idle low to minimise power dissipation.

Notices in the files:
PXF_CAPE_PCB/PixHawk_Fire_v1.5.brd:
(c)2014  PR,LM,3DR,AT,BN,AP
